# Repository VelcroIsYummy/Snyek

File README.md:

# Nitinol Based Snake Robot With Custom Designed Hardware and Software.
## (A Snakebot)[https://en.wikipedia.org/wiki/Snakebot] designed to explore and patrol autonomously.

This project is for the 2027 CARSF Science Fair, we plan to program it entirely in baremetal ASM. This project's CAD files are currently being designed in Autodesk Fusion. We have intent to add the following features:
- CV
- CSI-2
- BMS 1S12P 16500s
- Muscle driving
- Lidar

 # Contributing
 Don't break anything.

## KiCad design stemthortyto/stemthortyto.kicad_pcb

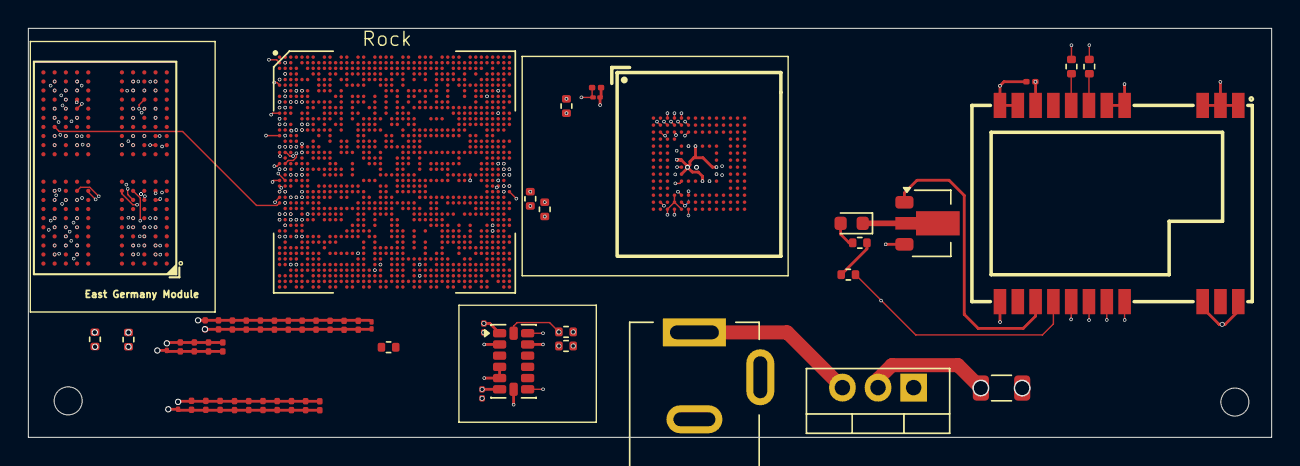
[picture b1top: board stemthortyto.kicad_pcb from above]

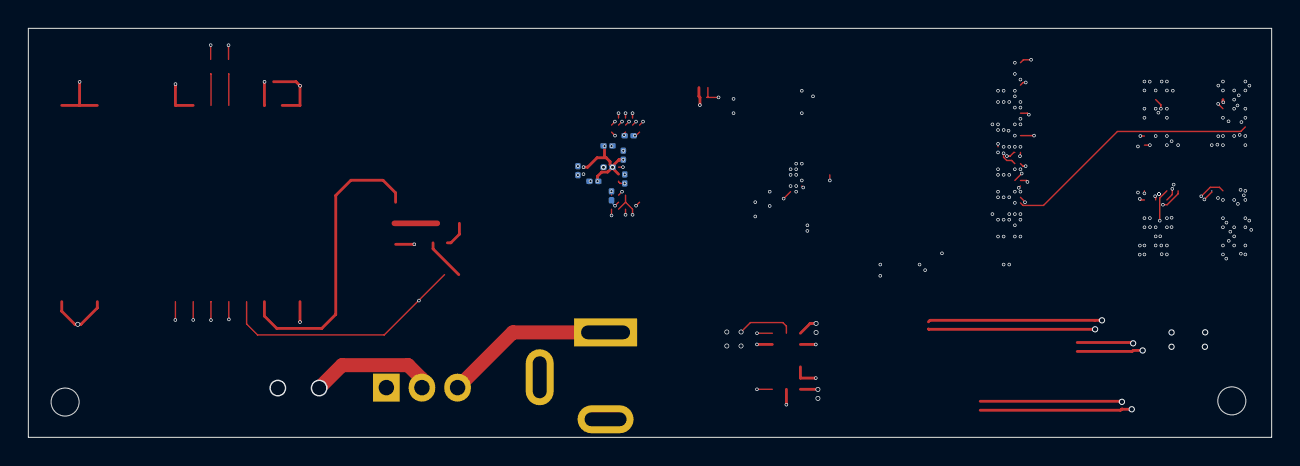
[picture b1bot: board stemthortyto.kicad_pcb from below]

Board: 8 copper layers, 88.7 x 29.2 mm, 64 parts (8 on the bottom side), 130 nets.

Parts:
C1, C2, C3, C35, C37, C40, C42, C43, C45: 0.1μF; C_0201_0603Metric
C5, C6, C7, C8, C9, C10, C11, C12, C13, C14, C16, C17, C18, C19, C20, C21, C22, C23, C24, C25, C27, C28, C29, C30, C31, C32: 0.1μf; C_0201_0603Metric
C15, C26, C39: 4.7μf; C_01005_0402Metric
C33: 1μf; C_0201_0603Metric
C34: 10pF; C_0201_0603Metric
C36: 4.7μF; C_0201_0603Metric
C38: 4.7μF; C_01005_0402Metric
C41: 22μF; C_1206_3216Metric
D1: LED; LED_0603_1608Metric
IC1: E22-900M22S; WIRELM-SMD_E22-900M22S
J1: Jack-DC; BarrelJack_Kycon_KLDX-0202-xC_Horizontal
Q1: BCV29; SOT-89-3
R1, R2: 2.7K; R_0402_1005Metric
R3: 4.7K; R_0402_1005Metric
R4: 48; R_0402_1005Metric
R5, R6: 200; R_0402_1005Metric
R7, R8: 240; R_0402_1005Metric
R9, R11, R12: 10K; R_0402_1005Metric
R10: 4.7k; R_0402_1005Metric
U1: LT1585-3.3; TO-220-3_Vertical
U2: ADXL343; LGA-14_3x5mm_P0.8mm_LayoutBorder1x6y
U3: RK3588S; FCCSP1253L
U4: K4UCE3Q4AB-MGCL; FBGA-200_L15.0-W10.0-BL_RS512M32LO4D1BDS-53BT
U5: FEMDRW032G-88A19; FBGA-153_L13.0-W11.5-P0.50_KLMAG1JETD-B041

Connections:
+1V1: C16.1, C17.1, C18.1, C19.1, C20.1, C21.1, C22.1, C23.1, C24.1, C25.1, C26.1, C27.1, C28.1, U4.A4 (VDD2), U4.A9 (VDD2), U4.AB4 (VDD2), U4.AB9 (VDD2), U4.F5 (VDD2), U4.F8 (VDD2), U4.H1 (VDD2), U4.H5 (VDD2), U4.H8 (VDD2), U4.H12 (VDD2), U4.K1 (VDD2), U4.K3 (VDD2), U4.K10 (VDD2), U4.K12 (VDD2), U4.N1 (VDD2), U4.N3 (VDD2), U4.N10 (VDD2), U4.N12 (VDD2), U4.R1 (VDD2), U4.R5 (VDD2), U4.R8 (VDD2), U4.R12 (VDD2), U4.U5 (VDD2), U4.U8 (VDD2)
+1V8: C29.1, C30.1, C31.1, C32.1, C39.1, U4.F1 (VDD1), U4.F12 (VDD1), U4.G4 (VDD1), U4.G9 (VDD1), U4.T4 (VDD1), U4.T9 (VDD1), U4.U1 (VDD1), U4.U12 (VDD1)
+3.3V: C1.2, C2.2, C3.1, C36.1, C37.1, C41.1, C42.1, C43.1, C45.1, IC1.9 (VCC), R1.1, R2.1, R3.1, R4.1, U1.2 (VO), U2.1 (Vdd_I/O), U2.6 (Vs), U2.7 (~CS), U5.E6 (VCC), U5.F5 (VCC), U5.J10 (VCC), U5.K9 (VCC)
A0A: U3.U1 (DDR_CH0_A0_A), U4.H2 (CA0_a)
A0B: U3.U2 (DDR_CH0_A0_B), U4.R2 (CA0_b)
A1A: U3.AC2 (DDR_CH0_A1_A), U4.J2 (CA1_a)
A1B: U3.R2 (DDR_CH0_A1_B), U4.P2 (CA1_b)
A2A: U3.AF1 (DDR_CH0_A2_A), U4.H9 (CA2_a)
A2B: U3.R1 (DDR_CH0_A2_B), U4.R9 (CA2_b)
A3A: U3.AL2 (DDR_CH0_A3_A), U4.H10 (CA3_a)
A3B: U3.D2 (DDR_CH0_A3_B), U4.R10 (CA3_b)
A4A: U3.Y1 (DDR_CH0_A4_A), U4.H11 (CA4_a)
A4B: U3.E1 (DDR_CH0_A4_B), U4.R11 (CA4_b)
A5A: U3.AG2 (DDR_CH0_A5_A), U4.J11 (CA5_a)
A5B: U3.L1 (DDR_CH0_A5_B), U4.P11 (CA5_b)
ACCLINT: U2.8 (INT1), U3.AY26 (BT1120_D15/SPDIF1_TX_M2/PCIE20X1_2_PERS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)
CKA_N: U3.AA1 (DDR_CH0_CKB_A), U4.J9 (CK_c_a)
CKA_P: U3.AA2 (DDR_CH0_CK_A), U4.J8 (CK_t_a)
CKB_N: U3.V1 (DDR_CH0_CKB_B), U4.P9 (CK_c_b)
CKB_P: U3.V2 (DDR_CH0_CK_B), U4.P8 (CK_t_b)
CKE0A: U3.AK1 (DDR_CH0_LP4/4X_CKE0/LP5_CS0_A), U4.J4 (CKE0_a)
CKE0B: U3.H2 (DDR_CH0_LP4/4X_CKE0/LP5_CS0_B), U4.P4 (CKE0_b)
CKE1A: U3.AD1 (DDR_CH0_LP4/4X_CKE1/LP5_CS1_A), U4.J5 (CKE1_a)
CKE1B: U3.F1 (DDR_CH0_LP4/4X_CKE1/LP5_CS1_B), U4.P5 (CKE1_b)
CLKOUT: C34.1, U3.AB41 (EMMC_CLKOUT/GPIO2_A1_d), U5.M6 (CLK)
CMD: R11.2, U3.AE42 (EMMC_CMD/FSPI_CLK_M0/GPIO2_A0_u), U5.M5 (CMD)
CS0A: U3.Y2 (DDR_CH0_LP4/4X_CS0_A), U4.H4 (CS0_a)
CS0B: U3.J1 (DDR_CH0_LP4/4X_CS0_B), U4.R4 (CS0_b)
CS1A: U3.AC1 (DDR_CH0_LP4/4X_CS1_A), U4.H3 (CS1_a)
CS1B: U3.M1 (DDR_CH0_LP4/4X_CS1_B), U4.R3 (CS1_b)
DAT0: R12.2, U3.Y41 (EMMC_D0/FSPI_D0_M0/GPIO2_D0_u), U5.A3 (DAT0)
DAT1: U3.Y40 (EMMC_D1/FSPI_D1_M0/GPIO2_D1_u), U5.A4 (DAT1)
DAT2: U3.AA41 (EMMC_D2/FSPI_D2_M0/GPIO2_D2_u), U5.A5 (DAT2)
DAT3: U3.AA42 (EMMC_D3/FSPI_D3_M0/GPIO2_D3_u), U5.B2 (DAT3)
DAT4: U3.AB42 (EMMC_D4/I2C1_SCL_M3/UART5_RX_M2/GPIO2_D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), U5.B3 (DAT4)
DAT5: U3.AD42 (EMMC_D5/I2C1_SDA_M3/UART5_TX_M2/GPIO2_D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), U5.B4 (DAT5)
DAT6: U3.AD41 (EMMC_D6/FSPI_CS0N_M0/GPIO2_D6_u), U5.B5 (DAT6)
DAT7: U3.AE41 (EMMC_D7/FSPI_CS1N_M0/GPIO2_D7_u), U5.B6 (DAT7)
DATASTROBE: U3.AC40 (EMMC_DATA_STROBE/I2C2_SDA_M2/UART5_CTSN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), U5.H5 (DS)
DM0A: U3.AE1 (DDR_CH0_DM0_A), U4.C3 (DMI0_a)
DM0B: U3.V5 (DDR_CH0_DM0_B), U4.Y3 (DMI0_b)
DM1A: U3.AK4 (DDR_CH0_DM1_A), U4.C10 (DMI1_a)
DM1B: U3.G2 (DDR_CH0_DM1_B), U4.Y10 (DMI1_b)
DQ0A: U3.AJ2 (DDR_CH0_DQ0_A), U4.B2 (DQ0_a)
DQ0B: U3.P3 (DDR_CH0_DQ5_B), U4.AA2 (DQ0_b)
DQ1A: U3.AF3 (DDR_CH0_DQ7_A), U4.C2 (DQ1_a)
DQ1B: U3.U5 (DDR_CH0_DQ3_B), U4.Y2 (DQ1_b)
DQ2A: U3.AE5 (DDR_CH0_DQ5_A), U4.E2 (DQ2_a)
DQ2B: U3.N1 (DDR_CH0_DQ2_B), U4.V2 (DQ2_b)
DQ3A: U3.AB5 (DDR_CH0_DQ4_A), U4.F2 (DQ3_a)
DQ3B: U3.P4 (DDR_CH0_DQ4_B), U4.U2 (DQ3_b)
DQ4A: U3.AB4 (DDR_CH0_DQ1_A), U4.F4 (DQ4_a)
DQ4B: U3.U3 (DDR_CH0_DQ0_B), U4.U4 (DQ4_b)
DQ5A: U3.AB3 (DDR_CH0_DQ3_A), U4.E4 (DQ5_a)
DQ5B: U3.U4 (DDR_CH0_DQ6_B), U4.V4 (DQ5_b)
DQ6A: U3.AE2 (DDR_CH0_DQ6_A), U4.C4 (DQ6_a)
DQ6B: U3.AA5 (DDR_CH0_DQ1_B), U4.Y4 (DQ6_b)
DQ7A: U3.AJ1 (DDR_CH0_DQ2_A), U4.B4 (DQ7_a)
DQ7B: U3.P5 (DDR_CH0_DQ7_B), U4.AA4 (DQ7_b)
DQ8A: U3.AN5 (DDR_CH0_DQ9_A), U4.B11 (DQ8_a)
DQ8B: U3.G5 (DDR_CH0_DQ8_B), U4.AA11 (DQ8_b)
DQ9A: U3.AN4 (DDR_CH0_DQ10_A), U4.C11 (DQ9_a)
DQ9B: U3.G4 (DDR_CH0_DQ10_B), U4.Y11 (DQ9_b)
DQ10A: U3.AF4 (DDR_CH0_DQ14_A), U4.E11 (DQ10_a)
DQ10B: U3.N6 (DDR_CH0_DQ15_B), U4.V11 (DQ10_b)
DQ11A: U3.AF5 (DDR_CH0_DQ15_A), U4.F11 (DQ11_a)
DQ11B: U3.N5 (DDR_CH0_DQ12_B), U4.U11 (DQ11_b)
DQ12A: U3.AJ6 (DDR_CH0_DQ11_A), U4.F9 (DQ12_a)
DQ12B: U3.N2 (DDR_CH0_DQ13_B), U4.U9 (DQ12_b)
DQ13A: U3.AJ3 (DDR_CH0_DQ12_A), U4.E9 (DQ13_a)
DQ13B: U3.J3 (DDR_CH0_DQ9_B), U4.V9 (DQ13_b)
DQ14A: U3.AK3 (DDR_CH0_DQ13_A), U4.C9 (DQ14_a)
DQ14B: U3.J5 (DDR_CH0_DQ14_B), U4.Y9 (DQ14_b)
DQ15A: U3.AK5 (DDR_CH0_DQ8_A), U4.B9 (DQ15_a)
DQ15B: U3.J4 (DDR_CH0_DQ11_B), U4.AA9 (DQ15_b)
DQS0NA: U3.AN2 (DDR_CH0_DQS0N_A), U4.E3 (DQS0_c_a)
DQS0NB: U3.B1 (DDR_CH0_DQS0N_B), U4.V3 (DQS0_c_b)
DQS0PA: U3.AN1 (DDR_CH0_DQS0P_A), U4.D3 (DQS0_t_a)
DQS0PB: U3.B2 (DDR_CH0_DQS0P_B), U4.W3 (DQS0_t_b)
DQS1NA: U3.AV3 (DDR_CH0_DQS1N_A), U4.E10 (DQS1_c_a)
DQS1NB: U3.K2 (DDR_CH0_DQS1N_B), U4.V10 (DQS1_c_b)
DQS1PA: U3.AV4 (DDR_CH0_DQS1P_A), U4.D10 (DQS1_t_a)
DQS1PB: U3.K1 (DDR_CH0_DQS1P_B), U4.W10 (DQS1_t_b)
EMCIO: C38.1, C40.1, R9.1, R11.1, R12.1, U3.AB35 (EMMCIO_1V8), U3.AC35 (EMMCIO_1V8), U5.C6 (VCCQ), U5.M4 (VCCQ), U5.N4 (VCCQ), U5.P3 (VCCQ), U5.P5 (VCCQ)
GND: C1.1, C2.1, C3.2, C5.2, C6.2, C7.2, C8.2, C9.2, C10.2, C11.2, C12.2, C13.2, C14.2, C15.2, C16.2, C17.2, C18.2, C19.2, C20.2, C21.2, C22.2, C23.2, C24.2, C25.2, C26.2, C27.2, C28.2, C29.2, C30.2, C31.2, C32.2, C33.1, C34.2, C35.2, C36.2, C37.2, C38.2, C39.2, C40.2, C42.2, C43.2, C45.2, IC1.1 (GND), IC1.2 (GND), IC1.3 (GND), IC1.4 (GND), IC1.5 (GND), IC1.10 (GND), IC1.11 (GND), IC1.12 (GND), IC1.20 (GND), IC1.22 (GND), Q1.3 (E), R10.2, U2.2 (GND), U2.4 (GND), U2.5 (GND), U2.12 (SDO/ADDR), U4.A3 (VSS), U4.A10 (VSS), U4.AB3 (VSS), U4.AB5 (VSS), U4.AB8 (VSS), U4.AB10 (VSS), U4.C1 (VSS), U4.C5 (VSS), U4.C8 (VSS), U4.C12 (VSS), U4.D2 (VSS), U4.D4 (VSS), U4.D9 (VSS), U4.D11 (VSS), U4.E1 (VSS), U4.E5 (VSS), U4.E8 (VSS), U4.E12 (VSS), U4.G1 (VSS), U4.G3 (VSS), U4.G5 (VSS), U4.G8 (VSS), U4.G10 (VSS), U4.G12 (VSS), U4.J1 (VSS), U4.J3 (VSS), U4.J10 (VSS), U4.J12 (VSS), U4.K2 (VSS), U4.K4 (VSS), U4.K9 (VSS), U4.K11 (VSS), U4.N2 (VSS), U4.N4 (VSS), U4.N9 (VSS), U4.N11 (VSS), U4.P1 (VSS), U4.P3 (VSS), U4.P10 (VSS), U4.P12 (VSS), U4.T1 (VSS), U4.T3 (VSS), U4.T5 (VSS), U4.T8 (VSS), U4.T10 (VSS), U4.T12 (VSS), U4.V1 (VSS), U4.V5 (VSS), U4.V8 (VSS), U4.V12 (VSS), U4.W2 (VSS), U4.W4 (VSS), U4.W9 (VSS), U4.W11 (VSS), U4.Y1 (VSS), U4.Y5 (VSS), U4.Y8 (VSS), U4.Y12 (VSS), U5.C4 (VSSQ), U5.E7 (VSS), U5.G5 (VSS), U5.H10 (VSS), U5.J5 (VSS), U5.K8 (VSS), U5.N2 (VSSQ), U5.N5 (VSSQ), U5.P4 (VSSQ), U5.P6 (VSSQ)
LoRaBUSY: IC1.14 (BUSY), Q1.1 (B)
LoRaCS: IC1.19 (NSS), U3.AT15 (CIF_HREF/BT1120_D8/I2S1_SDO1_M0/PCIE20X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)
LoRaMISO: IC1.16 (MISO), U3.AV19 (CIF_D0/BT1120_D0/I2S1_MCLK_M0/PCIE20X1_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)
LoRaMOSI: IC1.17 (MOSI), U3.AW18 (CIF_D1/BT1120_D1/I2S1_SCLK_TX_M0/PCIE20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)
LoRaRST: IC1.15 (NRST), R3.2, U3.H38 (PDM1_SDI0_M1/PCIE20X1_1_PERSTN_M2/PWM3_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)
LoRaRX: IC1.6 (RXEN), R5.1
LoRaSCK(CK): IC1.18 (SCK), U3.AV26 (CIF_D2/BT1120_D2/I2S1_LRCK_TX_M0/PCIE20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)
LoRaTX: IC1.7 (TXEN), R6.1
unnamed: D1.2 (A), R4.2
unnamed: D1.1 (K), Q1.2 (C)
unnamed: C41.2, J1.2, U1.1 (GND)
unnamed: J1.1, U1.3 (VI)
unnamed: R5.2, U3.G40 (PCIE20X1_1_CLKREQN_M2/DP0_HPDIN_M2/I2C2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)
unnamed: R6.2, U3.L40 (PCIE20X1_1_WAKEN_M2/I2C2_SCL_M4/UART6_T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)
unnamed: U3.AA14 (AVSS[132]), U3.AA26 (AVSS[132]), U3.AL15 (AVSS[132]), U3.AM14 (AVSS[132]), U3.AM15 (AVSS[132]), U3.AN11 (AVSS[132]), U3.AN13 (AVSS[132]), U3.AN14 (AVSS[132]), U3.AN15 (AVSS[132]), U3.AN18 (AVSS[132]), U3.AP7 (AVSS[132]), U3.AP8 (AVSS[132]), U3.AP9 (AVSS[132]), U3.AP10 (AVSS[132]), U3.AP11 (AVSS[132]), U3.AP16 (AVSS[132]), U3.AP22 (AVSS[132]), U3.AP31 (AVSS[132]), U3.AP32 (AVSS[132]), U3.AR9 (AVSS[132]), U3.AR16 (AVSS[132]), U3.AR18 (AVSS[132]), U3.AR20 (AVSS[132]), U3.AR21 (AVSS[132]), U3.AR22 (AVSS[132]), U3.AR25 (AVSS[132]), U3.AT7 (AVSS[132]), U3.AT8 (AVSS[132]), U3.AT16 (AVSS[132]), U3.AT19 (AVSS[132]), U3.AT20 (AVSS[132]), U3.AT21 (AVSS[132]), U3.AT22 (AVSS[132]), U3.AT23 (AVSS[132]), U3.AT29 (AVSS[132]), U3.AU8 (AVSS[132]), U3.AU16 (AVSS[132]), U3.AU18 (AVSS[132]), U3.AU19 (AVSS[132]), U3.AU21 (AVSS[132]), U3.AU24 (AVSS[132]), U3.AU25 (AVSS[132]), U3.AU27 (AVSS[132]), U3.AU28 (AVSS[132]), U3.AU29 (AVSS[132]), U3.AU31 (AVSS[132]), U3.AV8 (AVSS[132]), U3.AV9 (AVSS[132]), U3.AV12 (AVSS[132]), U3.AV14 (AVSS[132]), U3.AV15 (AVSS[132]), U3.AV16 (AVSS[132]), U3.AV21 (AVSS[132]), U3.AV25 (AVSS[132]), U3.AV29 (AVSS[132]), U3.AV32 (AVSS[132]), U3.AV33 (AVSS[132]), U3.AW8 (AVSS[132]), U3.AW9 (AVSS[132]), U3.AW12 (AVSS[132]), U3.AW14 (AVSS[132]), U3.AW16 (AVSS[132]), U3.AW17 (AVSS[132]), U3.AW21 (AVSS[132]), U3.AW25 (AVSS[132]), U3.AW28 (AVSS[132]), U3.AW29 (AVSS[132]), U3.AW32 (AVSS[132]), U3.AW33 (AVSS[132]), U3.AW36 (AVSS[132]), U3.AW40 (AVSS[132]), U3.AY2 (AVSS[132]), U3.AY4 (AVSS[132]), U3.AY5 (AVSS[132]), U3.AY7 (AVSS[132]), U3.AY8 (AVSS[132]), U3.AY9 (AVSS[132]), U3.AY12 (AVSS[132]), U3.AY14 (AVSS[132]), U3.AY16 (AVSS[132]), U3.AY17 (AVSS[132]), U3.AY18 (AVSS[132]), U3.AY21 (AVSS[132]), U3.AY22 (AVSS[132]), U3.AY23 (AVSS[132]), U3.AY25 (AVSS[132]), U3.AY28 (AVSS[132]), U3.AY29 (AVSS[132]), U3.AY32 (AVSS[132]), U3.AY33 (AVSS[132]), U3.AY36 (AVSS[132]), U3.AY37 (AVSS[132]), U3.AY39 (AVSS[132]), U3.AY41 (AVSS[132]), U3.BA3 (AVSS[132]), U3.BA6 (AVSS[132]), U3.BA9 (AVSS[132]), U3.BA12 (AVSS[132]), U3.BA15 (AVSS[132]), U3.BA18 (AVSS[132]), U3.BA21 (AVSS[132]), U3.BA24 (AVSS[132]), U3.BA27 (AVSS[132]), U3.BA30 (AVSS[132]), U3.BA33 (AVSS[132]), U3.BA36 (AVSS[132]), U3.BB1 (AVSS[132]), U3.BB42 (AVSS[132]), U3.C41 (AVSS[132]), U3.E40 (AVSS[132]), U3.F40 (AVSS[132]), U3.G36 (AVSS[132]), U3.G41 (AVSS[132]), U3.H37 (AVSS[132]), U3.H40 (AVSS[132]), U3.J38 (AVSS[132]), U3.J39 (AVSS[132]), U3.J40 (AVSS[132]), U3.K34 (AVSS[132]), U3.K35 (AVSS[132]), U3.K36 (AVSS[132]), U3.K37 (AVSS[132]), U3.K38 (AVSS[132]), U3.K39 (AVSS[132]), U3.K40 (AVSS[132]), U3.L34 (AVSS[132]), U3.L35 (AVSS[132]), U3.L41 (AVSS[132]), U3.M33 (AVSS[132]), U3.M34 (AVSS[132]), U3.N15 (AVSS[132]), U3.N33 (AVSS[132])
unnamed: U3.P10 (DDR_CH0_VDDQ[6]), U3.R10 (DDR_CH0_VDDQ[6]), U3.T10 (DDR_CH0_VDDQ[6]), U3.V10 (DDR_CH0_VDDQ[6]), U3.W10 (DDR_CH0_VDDQ[6]), U3.Y10 (DDR_CH0_VDDQ[6])
unnamed: U3.T12 (DDR_CH0_VDD[4]), U3.T13 (DDR_CH0_VDD[4]), U3.U12 (DDR_CH0_VDD[4]), U3.U13 (DDR_CH0_VDD[4])
unnamed: U3.V12 (DDR_CH0_VDD_MIF[3]), U3.V13 (DDR_CH0_VDD_MIF[3]), U3.V14 (DDR_CH0_VDD_MIF[3])
unnamed: U3.H14 (DDR_CH1_VDDQ[5]), U3.H15 (DDR_CH1_VDDQ[5]), U3.H16 (DDR_CH1_VDDQ[5]), U3.H18 (DDR_CH1_VDDQ[5]), U3.H20 (DDR_CH1_VDDQ[5])
unnamed: U3.J18 (DDR_CH1_VDD[3]), U3.K18 (DDR_CH1_VDD[3]), U3.L18 (DDR_CH1_VDD[3])
unnamed: U3.J20 (DDR_CH1_VDD_MIF[3]), U3.K20 (DDR_CH1_VDD_MIF[3]), U3.L20 (DDR_CH1_VDD_MIF[3])
unnamed: U3.AM13 (HDMI/eDP_TX0_VDD_0V75[2]), U3.AN12 (HDMI/eDP_TX0_VDD_0V75[2])
unnamed: U3.AP18 (TYPEC0_DP0_VDDA_0V85[2]), U3.AR19 (TYPEC0_DP0_VDDA_0V85[2])
unnamed: U3.G27 (VCCIO4_1V8[2]), U3.G28 (VCCIO4_1V8[2])
unnamed: U3.AC33 (VCCIO5[2]), U3.AC34 (VCCIO5[2])
unnamed: U3.AL33 (VCCIO6[2]), U3.AM33 (VCCIO6[2])
unnamed: U3.K27 (VDD_CPU_BIG0[14]), U3.K28 (VDD_CPU_BIG0[14]), U3.K29 (VDD_CPU_BIG0[14]), U3.K30 (VDD_CPU_BIG0[14]), U3.M24 (VDD_CPU_BIG0[14]), U3.M25 (VDD_CPU_BIG0[14]), U3.M28 (VDD_CPU_BIG0[14]), U3.M29 (VDD_CPU_BIG0[14]), U3.M30 (VDD_CPU_BIG0[14]), U3.N24 (VDD_CPU_BIG0[14]), U3.N25 (VDD_CPU_BIG0[14]), U3.P23 (VDD_CPU_BIG0[14]), U3.R23 (VDD_CPU_BIG0[14]), U3.R24 (VDD_CPU_BIG0[14])
unnamed: U3.R26 (VDD_CPU_BIG1[14]), U3.R27 (VDD_CPU_BIG1[14]), U3.R28 (VDD_CPU_BIG1[14]), U3.R29 (VDD_CPU_BIG1[14]), U3.R30 (VDD_CPU_BIG1[14]), U3.R31 (VDD_CPU_BIG1[14]), U3.R32 (VDD_CPU_BIG1[14]), U3.R33 (VDD_CPU_BIG1[14]), U3.T26 (VDD_CPU_BIG1[14]), U3.U26 (VDD_CPU_BIG1[14]), U3.V26 (VDD_CPU_BIG1[14]), U3.V27 (VDD_CPU_BIG1[14]), U3.V28 (VDD_CPU_BIG1[14]), U3.V29 (VDD_CPU_BIG1[14])
unnamed: U3.AA28 (VDD_CPU_LIT[12]), U3.AA29 (VDD_CPU_LIT[12]), U3.AA30 (VDD_CPU_LIT[12]), U3.AB31 (VDD_CPU_LIT[12]), U3.AC27 (VDD_CPU_LIT[12]), U3.AC28 (VDD_CPU_LIT[12]), U3.AC29 (VDD_CPU_LIT[12]), U3.AC30 (VDD_CPU_LIT[12]), U3.AC31 (VDD_CPU_LIT[12]), U3.AD26 (VDD_CPU_LIT[12]), U3.AD27 (VDD_CPU_LIT[12]), U3.AE27 (VDD_CPU_LIT[12])
unnamed: U3.AH18 (VDD_GPU[13]), U3.AH19 (VDD_GPU[13]), U3.AH20 (VDD_GPU[13]), U3.AH21 (VDD_GPU[13]), U3.AJ19 (VDD_GPU[13]), U3.AJ20 (VDD_GPU[13]), U3.AJ21 (VDD_GPU[13]), U3.AK21 (VDD_GPU[13]), U3.AL21 (VDD_GPU[13]), U3.AM21 (VDD_GPU[13]), U3.AM22 (VDD_GPU[13]), U3.AN21 (VDD_GPU[13]), U3.AN22 (VDD_GPU[13])
unnamed: U3.AJ18 (VDD_GPU_MEM[3]), U3.AK18 (VDD_GPU_MEM[3]), U3.AL18 (VDD_GPU_MEM[3])
unnamed: U3.AF12 (VDD_LOGIC[18]), U3.AF13 (VDD_LOGIC[18]), U3.AH11 (VDD_LOGIC[18]), U3.AH12 (VDD_LOGIC[18]), U3.AH13 (VDD_LOGIC[18]), U3.AH14 (VDD_LOGIC[18]), U3.AH15 (VDD_LOGIC[18]), U3.AH23 (VDD_LOGIC[18]), U3.AH24 (VDD_LOGIC[18]), U3.AJ15 (VDD_LOGIC[18]), U3.AJ31 (VDD_LOGIC[18]), U3.AJ32 (VDD_LOGIC[18]), U3.AK15 (VDD_LOGIC[18]), U3.AL31 (VDD_LOGIC[18]), U3.H27 (VDD_LOGIC[18]), U3.J27 (VDD_LOGIC[18]), U3.W33 (VDD_LOGIC[18]), U3.Y33 (VDD_LOGIC[18])
unnamed: U3.AK27 (VDD_NPU[9]), U3.AK28 (VDD_NPU[9]), U3.AK29 (VDD_NPU[9]), U3.AL28 (VDD_NPU[9]), U3.AL29 (VDD_NPU[9]), U3.AL30 (VDD_NPU[9]), U3.AM30 (VDD_NPU[9]), U3.AN30 (VDD_NPU[9]), U3.AP30 (VDD_NPU[9])
unnamed: U3.AH25 (VDD_NPU_MEM[4]), U3.AH26 (VDD_NPU_MEM[4]), U3.AJ25 (VDD_NPU_MEM[4]), U3.AK25 (VDD_NPU_MEM[4])
unnamed: U3.AC16 (VDD_VDENC[9]), U3.AD15 (VDD_VDENC[9]), U3.P15 (VDD_VDENC[9]), U3.R15 (VDD_VDENC[9]), U3.T15 (VDD_VDENC[9]), U3.U15 (VDD_VDENC[9]), U3.W16 (VDD_VDENC[9]), U3.W17 (VDD_VDENC[9]), U3.Y17 (VDD_VDENC[9])
unnamed: U3.A1 (VSS[533]), U3.A2 (VSS[533]), U3.A42 (VSS[533]), U3.AA3 (VSS[533]), U3.AA6 (VSS[533]), U3.AA7 (VSS[533]), U3.AA8 (VSS[533]), U3.AA9 (VSS[533]), U3.AA10 (VSS[533]), U3.AA11 (VSS[533]), U3.AA12 (VSS[533]), U3.AA19 (VSS[533]), U3.AA22 (VSS[533]), U3.AA23 (VSS[533]), U3.AA31 (VSS[533]), U3.AA37 (VSS[533]), U3.AA38 (VSS[533]), U3.AA39 (VSS[533]), U3.AA40 (VSS[533]), U3.AB2 (VSS[533]), U3.AB6 (VSS[533]), U3.AB9 (VSS[533]), U3.AB10 (VSS[533]), U3.AB11 (VSS[533]), U3.AB12 (VSS[533]), U3.AB19 (VSS[533]), U3.AB20 (VSS[533]), U3.AB21 (VSS[533]), U3.AB22 (VSS[533]), U3.AB23 (VSS[533]), U3.AB24 (VSS[533]), U3.AB32 (VSS[533]), U3.AB33 (VSS[533]), U3.AB34 (VSS[533]), U3.AB36 (VSS[533]), U3.AB37 (VSS[533]), U3.AB38 (VSS[533]), U3.AB39 (VSS[533]), U3.AB40 (VSS[533]), U3.AC3 (VSS[533]), U3.AC4 (VSS[533]), U3.AC5 (VSS[533]), U3.AC6 (VSS[533]), U3.AC17 (VSS[533]), U3.AC18 (VSS[533]), U3.AC22 (VSS[533]), U3.AC23 (VSS[533]), U3.AC24 (VSS[533]), U3.AC25 (VSS[533]), U3.AC26 (VSS[533]), U3.AC41 (VSS[533]), U3.AD2 (VSS[533]), U3.AD3 (VSS[533]), U3.AD5 (VSS[533]), U3.AD6 (VSS[533]), U3.AD8 (VSS[533]), U3.AD9 (VSS[533]), U3.AD10 (VSS[533]), U3.AD11 (VSS[533]), U3.AD12 (VSS[533]), U3.AD13 (VSS[533]), U3.AD14 (VSS[533]), U3.AD19 (VSS[533]), U3.AD20 (VSS[533]), U3.AD22 (VSS[533]), U3.AD23 (VSS[533]), U3.AD24 (VSS[533]), U3.AD25 (VSS[533]), U3.AE6 (VSS[533]), U3.AE7 (VSS[533]), U3.AE8 (VSS[533]), U3.AE9 (VSS[533]), U3.AE10 (VSS[533]), U3.AE11 (VSS[533]), U3.AE12 (VSS[533]), U3.AE13 (VSS[533]), U3.AE14 (VSS[533]), U3.AE15 (VSS[533]), U3.AE16 (VSS[533]), U3.AE19 (VSS[533]), U3.AE20 (VSS[533]), U3.AE22 (VSS[533]), U3.AE23 (VSS[533]), U3.AE24 (VSS[533]), U3.AE25 (VSS[533]), U3.AE26 (VSS[533]), U3.AE38 (VSS[533]), U3.AE39 (VSS[533]), U3.AE40 (VSS[533]), U3.AF2 (VSS[533]), U3.AF6 (VSS[533]), U3.AF7 (VSS[533]), U3.AF8 (VSS[533]), U3.AF9 (VSS[533]), U3.AF10 (VSS[533]), U3.AF16 (VSS[533]), U3.AF17 (VSS[533]), U3.AF19 (VSS[533]), U3.AF20 (VSS[533]), U3.AF21 (VSS[533]), U3.AF26 (VSS[533]), U3.AF27 (VSS[533]), U3.AF28 (VSS[533]), U3.AF29 (VSS[533]), U3.AF30 (VSS[533]), U3.AF31 (VSS[533]), U3.AF32 (VSS[533]), U3.AF33 (VSS[533]), U3.AF34 (VSS[533]), U3.AF37 (VSS[533]), U3.AF38 (VSS[533]), U3.AF39 (VSS[533]), U3.AF40 (VSS[533]), U3.AF41 (VSS[533]), U3.AG3 (VSS[533]), U3.AG4 (VSS[533]), U3.AG5 (VSS[533]), U3.AG6 (VSS[533]), U3.AG7 (VSS[533]), U3.AG8 (VSS[533]), U3.AG15 (VSS[533]), U3.AG16 (VSS[533]), U3.AG17 (VSS[533]), U3.AG18 (VSS[533]), U3.AG19 (VSS[533]), U3.AG20 (VSS[533]), U3.AG21 (VSS[533]), U3.AG22 (VSS[533]), U3.AG23 (VSS[533]), U3.AG24 (VSS[533]), U3.AG25 (VSS[533]), U3.AG28 (VSS[533]), U3.AG29 (VSS[533]), U3.AG31 (VSS[533]), U3.AG32 (VSS[533]), U3.AG33 (VSS[533]), U3.AG34 (VSS[533]), U3.AG35 (VSS[533]), U3.AG40 (VSS[533]), U3.AH2 (VSS[533]), U3.AH3 (VSS[533]), U3.AH4 (VSS[533]), U3.AH5 (VSS[533]), U3.AH7 (VSS[533]), U3.AH8 (VSS[533]), U3.AH9 (VSS[533]), U3.AH10 (VSS[533]), U3.AH16 (VSS[533]), U3.AH17 (VSS[533]), U3.AH28 (VSS[533]), U3.AH29 (VSS[533]), U3.AH36 (VSS[533]), U3.AJ5 (VSS[533]), U3.AJ7 (VSS[533]), U3.AJ8 (VSS[533]), U3.AJ9 (VSS[533]), U3.AJ10 (VSS[533]), U3.AJ11 (VSS[533]), U3.AJ12 (VSS[533]), U3.AJ16 (VSS[533]), U3.AJ26 (VSS[533]), U3.AJ27 (VSS[533]), U3.AJ28 (VSS[533]), U3.AJ29 (VSS[533]), U3.AJ30 (VSS[533]), U3.AJ35 (VSS[533]), U3.AJ38 (VSS[533]), U3.AJ39 (VSS[533]), U3.AJ40 (VSS[533]), U3.AJ41 (VSS[533]), U3.AK2 (VSS[533]), U3.AK6 (VSS[533]), U3.AK7 (VSS[533]), U3.AK16 (VSS[533]), U3.AK22 (VSS[533]), U3.AK26 (VSS[533]), U3.AK30 (VSS[533]), U3.AK40 (VSS[533]), U3.AL3 (VSS[533]), U3.AL4 (VSS[533]), U3.AL5 (VSS[533]), U3.AL16 (VSS[533]), U3.AL22 (VSS[533]), U3.AL35 (VSS[533]), U3.AM4 (VSS[533]), U3.AM5 (VSS[533]), U3.AM16 (VSS[533]), U3.AM17 (VSS[533]), U3.AM23 (VSS[533]), U3.AM25 (VSS[533]), U3.AM27 (VSS[533]), U3.AM31 (VSS[533]), U3.AM32 (VSS[533]), U3.AM41 (VSS[533]), U3.AN3 (VSS[533]), U3.AN6 (VSS[533]), U3.AN7 (VSS[533]), U3.AN17 (VSS[533]), U3.AN23 (VSS[533]), U3.AN25 (VSS[533]), U3.AN31 (VSS[533]), U3.AN32 (VSS[533]), U3.AN33 (VSS[533]), U3.AN34 (VSS[533]), U3.AN35 (VSS[533]), U3.AN37 (VSS[533]), U3.AN38 (VSS[533]), U3.AN39 (VSS[533]), U3.AN40 (VSS[533]), U3.AP2 (VSS[533]), U3.AP5 (VSS[533]), U3.AP6 (VSS[533]), U3.AP25 (VSS[533]), U3.AP27 (VSS[533]), U3.AP33 (VSS[533]), U3.AP34 (VSS[533]), U3.AP35 (VSS[533]), U3.AP37 (VSS[533]), U3.AP38 (VSS[533]), U3.AP39 (VSS[533]), U3.AP40 (VSS[533]), U3.AR3 (VSS[533]), U3.AR4 (VSS[533]), U3.AR40 (VSS[533]), U3.AR41 (VSS[533]), U3.AT2 (VSS[533]), U3.AT5 (VSS[533]), U3.AT6 (VSS[533]), U3.AT36 (VSS[533]), U3.AU2 (VSS[533]), U3.AU3 (VSS[533]), U3.AU4 (VSS[533]), U3.AU35 (VSS[533]), U3.AU38 (VSS[533]), U3.AU39 (VSS[533]), U3.AU40 (VSS[533]), U3.AV5 (VSS[533]), U3.AV36 (VSS[533]), U3.AV41 (VSS[533]), U3.AW3 (VSS[533]), U3.AW4 (VSS[533]), U3.B3 (VSS[533]), U3.B5 (VSS[533]), U3.B8 (VSS[533]), U3.B10 (VSS[533]), U3.B11 (VSS[533]), U3.B14 (VSS[533]), U3.B17 (VSS[533]), U3.B19 (VSS[533]), U3.B21 (VSS[533]), U3.B23 (VSS[533]), U3.B26 (VSS[533]), U3.B27 (VSS[533]), U3.B29 (VSS[533]), U3.B31 (VSS[533]), U3.B34 (VSS[533]), U3.B35 (VSS[533]), U3.B36 (VSS[533]), U3.B38 (VSS[533]), U3.B40 (VSS[533]), U3.B42 (VSS[533]), U3.C2 (VSS[533]), U3.C6 (VSS[533]), U3.C7 (VSS[533]), U3.C9 (VSS[533]), U3.C11 (VSS[533]), U3.C12 (VSS[533]), U3.C14 (VSS[533]), U3.C15 (VSS[533]), U3.C18 (VSS[533]), U3.C19 (VSS[533]), U3.C20 (VSS[533]), U3.C22 (VSS[533]), U3.C24 (VSS[533]), U3.C26 (VSS[533]), U3.C28 (VSS[533]), U3.C30 (VSS[533]), U3.C35 (VSS[533]), U3.C37 (VSS[533]), U3.C39 (VSS[533]), U3.D3 (VSS[533]), U3.D4 (VSS[533]), U3.D7 (VSS[533]), U3.D11 (VSS[533]), U3.D14 (VSS[533]), U3.D15 (VSS[533]), U3.D18 (VSS[533]), U3.D19 (VSS[533]), U3.D22 (VSS[533]), U3.D26 (VSS[533]), U3.D30 (VSS[533]), U3.D31 (VSS[533]), U3.D32 (VSS[533]), U3.E2 (VSS[533]), U3.E5 (VSS[533]), U3.E6 (VSS[533]), U3.E8 (VSS[533]), U3.E9 (VSS[533]), U3.E10 (VSS[533]), U3.E12 (VSS[533]), U3.E16 (VSS[533]), U3.E18 (VSS[533]), U3.E19 (VSS[533]), U3.E21 (VSS[533]), U3.E23 (VSS[533]), U3.E25 (VSS[533]), U3.E27 (VSS[533]), U3.E30 (VSS[533]), U3.E31 (VSS[533]), U3.E33 (VSS[533]), U3.E34 (VSS[533]), U3.E37 (VSS[533]), U3.E38 (VSS[533]), U3.E39 (VSS[533]), U3.F2 (VSS[533]), U3.F3 (VSS[533]), U3.F4 (VSS[533]), U3.F8 (VSS[533]), U3.F9 (VSS[533]), U3.F10 (VSS[533]), U3.F13 (VSS[533]), U3.F14 (VSS[533]), U3.F15 (VSS[533]), U3.F16 (VSS[533]), U3.F19 (VSS[533]), U3.F21 (VSS[533]), U3.F23 (VSS[533]), U3.F29 (VSS[533]), U3.F31 (VSS[533]), U3.F33 (VSS[533]), U3.F34 (VSS[533]), U3.F35 (VSS[533]), U3.F36 (VSS[533]), U3.F38 (VSS[533]), U3.F39 (VSS[533]), U3.G3 (VSS[533]), U3.G6 (VSS[533]), U3.G8 (VSS[533]), U3.G9 (VSS[533]), U3.G10 (VSS[533]), U3.G12 (VSS[533]), U3.G20 (VSS[533]), U3.G21 (VSS[533]), U3.G22 (VSS[533]), U3.G25 (VSS[533]), U3.G26 (VSS[533]), U3.G29 (VSS[533]), U3.H3 (VSS[533]), U3.H4 (VSS[533]), U3.H5 (VSS[533]), U3.H6 (VSS[533]), U3.H11 (VSS[533]), U3.H12 (VSS[533]), U3.H22 (VSS[533]), U3.H25 (VSS[533]), U3.H29 (VSS[533]), U3.J2 (VSS[533]), U3.J6 (VSS[533]), U3.J7 (VSS[533]), U3.J8 (VSS[533]), U3.J9 (VSS[533]), U3.J10 (VSS[533]), U3.J12 (VSS[533]), U3.J14 (VSS[533]), U3.J15 (VSS[533]), U3.J16 (VSS[533]), U3.J22 (VSS[533]), U3.J24 (VSS[533]), U3.J26 (VSS[533]), U3.J29 (VSS[533]), U3.J30 (VSS[533]), U3.J31 (VSS[533]), U3.K3 (VSS[533]), U3.K6 (VSS[533]), U3.K7 (VSS[533]), U3.K10 (VSS[533]), U3.K11 (VSS[533]), U3.K12 (VSS[533]), U3.K14 (VSS[533]), U3.K17 (VSS[533]), U3.K22 (VSS[533]), U3.K23 (VSS[533]), U3.K25 (VSS[533]), U3.K26 (VSS[533]), U3.K31 (VSS[533]), U3.K32 (VSS[533]), U3.K33 (VSS[533]), U3.L2 (VSS[533]), U3.L3 (VSS[533]), U3.L5 (VSS[533]), U3.L6 (VSS[533]), U3.L10 (VSS[533]), U3.L11 (VSS[533]), U3.L12 (VSS[533]), U3.L14 (VSS[533]), U3.L22 (VSS[533]), U3.L23 (VSS[533]), U3.L24 (VSS[533]), U3.L32 (VSS[533]), U3.L33 (VSS[533]), U3.L36 (VSS[533]), U3.M2 (VSS[533]), U3.M5 (VSS[533]), U3.M8 (VSS[533]), U3.M9 (VSS[533]), U3.M10 (VSS[533]), U3.M12 (VSS[533]), U3.M14 (VSS[533]), U3.M17 (VSS[533]), U3.M19 (VSS[533]), U3.M21 (VSS[533]), U3.M22 (VSS[533]), U3.M23 (VSS[533]), U3.M35 (VSS[533]), U3.M36 (VSS[533]), U3.N3 (VSS[533]), U3.N7 (VSS[533]), U3.N9 (VSS[533]), U3.N11 (VSS[533]), U3.N12 (VSS[533]), U3.N16 (VSS[533]), U3.N17 (VSS[533]), U3.N18 (VSS[533]), U3.N21 (VSS[533]), U3.N22 (VSS[533]), U3.N34 (VSS[533]), U3.N38 (VSS[533]), U3.N39 (VSS[533]), U3.N40 (VSS[533]), U3.P2 (VSS[533]), U3.P6 (VSS[533]), U3.P7 (VSS[533]), U3.P8 (VSS[533]), U3.P9 (VSS[533]), U3.P12 (VSS[533]), U3.P16 (VSS[533]), U3.P17 (VSS[533]), U3.P18 (VSS[533]), U3.P19 (VSS[533]), U3.P25 (VSS[533]), U3.P26 (VSS[533]), U3.P27 (VSS[533]), U3.P28 (VSS[533]), U3.P29 (VSS[533]), U3.P30 (VSS[533]), U3.P31 (VSS[533]), U3.P32 (VSS[533]), U3.P33 (VSS[533]), U3.P34 (VSS[533]), U3.R3 (VSS[533]), U3.R4 (VSS[533]), U3.R8 (VSS[533]), U3.R16 (VSS[533]), U3.R20 (VSS[533]), U3.R21 (VSS[533]), U3.R25 (VSS[533]), U3.R35 (VSS[533]), U3.T2 (VSS[533]), U3.T3 (VSS[533]), U3.T4 (VSS[533]), U3.T7 (VSS[533]), U3.T16 (VSS[533]), U3.T17 (VSS[533]), U3.T18 (VSS[533]), U3.T20 (VSS[533]), U3.T21 (VSS[533]), U3.T24 (VSS[533]), U3.T25 (VSS[533]), U3.T35 (VSS[533]), U3.T36 (VSS[533]), U3.T37 (VSS[533]), U3.T38 (VSS[533]), U3.T39 (VSS[533]), U3.T40 (VSS[533]), U3.U6 (VSS[533]), U3.U7 (VSS[533]), U3.U8 (VSS[533]), U3.U16 (VSS[533]), U3.U17 (VSS[533]), U3.U18 (VSS[533]), U3.U20 (VSS[533]), U3.U21 (VSS[533]), U3.U22 (VSS[533]), U3.U23 (VSS[533]), U3.U24 (VSS[533]), U3.U25 (VSS[533]), U3.U39 (VSS[533]), U3.U40 (VSS[533]), U3.U41 (VSS[533]), U3.V3 (VSS[533]), U3.V6 (VSS[533]), U3.V7 (VSS[533]), U3.V8 (VSS[533]), U3.V16 (VSS[533]), U3.V17 (VSS[533]), U3.V19 (VSS[533]), U3.V23 (VSS[533]), U3.V24 (VSS[533]), U3.V25 (VSS[533]), U3.V30 (VSS[533]), U3.V31 (VSS[533]), U3.V32 (VSS[533]), U3.V33 (VSS[533]), U3.V34 (VSS[533]), U3.V38 (VSS[533]), U3.V39 (VSS[533]), U3.V40 (VSS[533]), U3.W2 (VSS[533]), U3.W5 (VSS[533]), U3.W7 (VSS[533]), U3.W8 (VSS[533]), U3.W9 (VSS[533]), U3.W18 (VSS[533]), U3.W19 (VSS[533]), U3.W22 (VSS[533]), U3.W23 (VSS[533]), U3.W24 (VSS[533]), U3.W26 (VSS[533]), U3.Y3 (VSS[533]), U3.Y4 (VSS[533]), U3.Y5 (VSS[533]), U3.Y6 (VSS[533]), U3.Y11 (VSS[533]), U3.Y18 (VSS[533]), U3.Y19 (VSS[533]), U3.Y22 (VSS[533]), U3.Y23 (VSS[533]), U3.Y24 (VSS[533]), U3.Y28 (VSS[533]), U3.Y29 (VSS[533]), U3.Y30 (VSS[533]), U3.Y31 (VSS[533]), U3.Y32 (VSS[533])
unnamed: R10.1, U4.G2 (ODT_CA_a1)/2)), U4.T2 (ODT_CA_b1)/2))
unnamed: R7.2, U4.A5 (ZQ0)
unnamed: R8.2, U4.A8 (ZQ1)
unnamed: C33.2, U5.C2 (VDDI)
RESETA: U3.AG1 (DDR_CH0_RESET_A), U4.T11 (RESET_n)
RST: C35.1, R9.2, U3.AD40 (EMMC_RSTN/I2C2_SCL_M2/UART5_RTSN_M1/GPI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), U5.K5 (RSTN)
SCLACCL: R2.2, U2.14 (SCL/SCLK), U3.AH39 (I2S1_MCLK_M1/JTAG_TCK_M2/I2C1_SCL_M0/UA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), U3.AL39 (I2S1_SDO2_M1/PDM0_SDI2_M1/PWM3_IR_M0/I2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)
SDAACCL: R1.2, U2.13 (SDA/SDI/SDIO), U3.AH40 (I2S1_SCLK_TX_M1/JTAG_TMS_M2/I2C1_SDA_M0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), U3.AM39 (I2S1_SDO3_M1/CPU_BIG1_AVS/I2C1_SDA_M2/C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)
ZQ0: C5.1, C6.1, C7.1, C8.1, C9.1, C10.1, C11.1, C12.1, C13.1, C14.1, C15.1, R7.1, R8.1, U4.AA3 (VDDQ), U4.AA5 (VDDQ), U4.AA8 (VDDQ), U4.AA10 (VDDQ), U4.B3 (VDDQ), U4.B5 (VDDQ), U4.B8 (VDDQ), U4.B10 (VDDQ), U4.D1 (VDDQ), U4.D5 (VDDQ), U4.D8 (VDDQ), U4.D12 (VDDQ), U4.F3 (VDDQ), U4.F10 (VDDQ), U4.U3 (VDDQ), U4.U10 (VDDQ), U4.W1 (VDDQ), U4.W5 (VDDQ), U4.W8 (VDDQ), U4.W12 (VDDQ)
